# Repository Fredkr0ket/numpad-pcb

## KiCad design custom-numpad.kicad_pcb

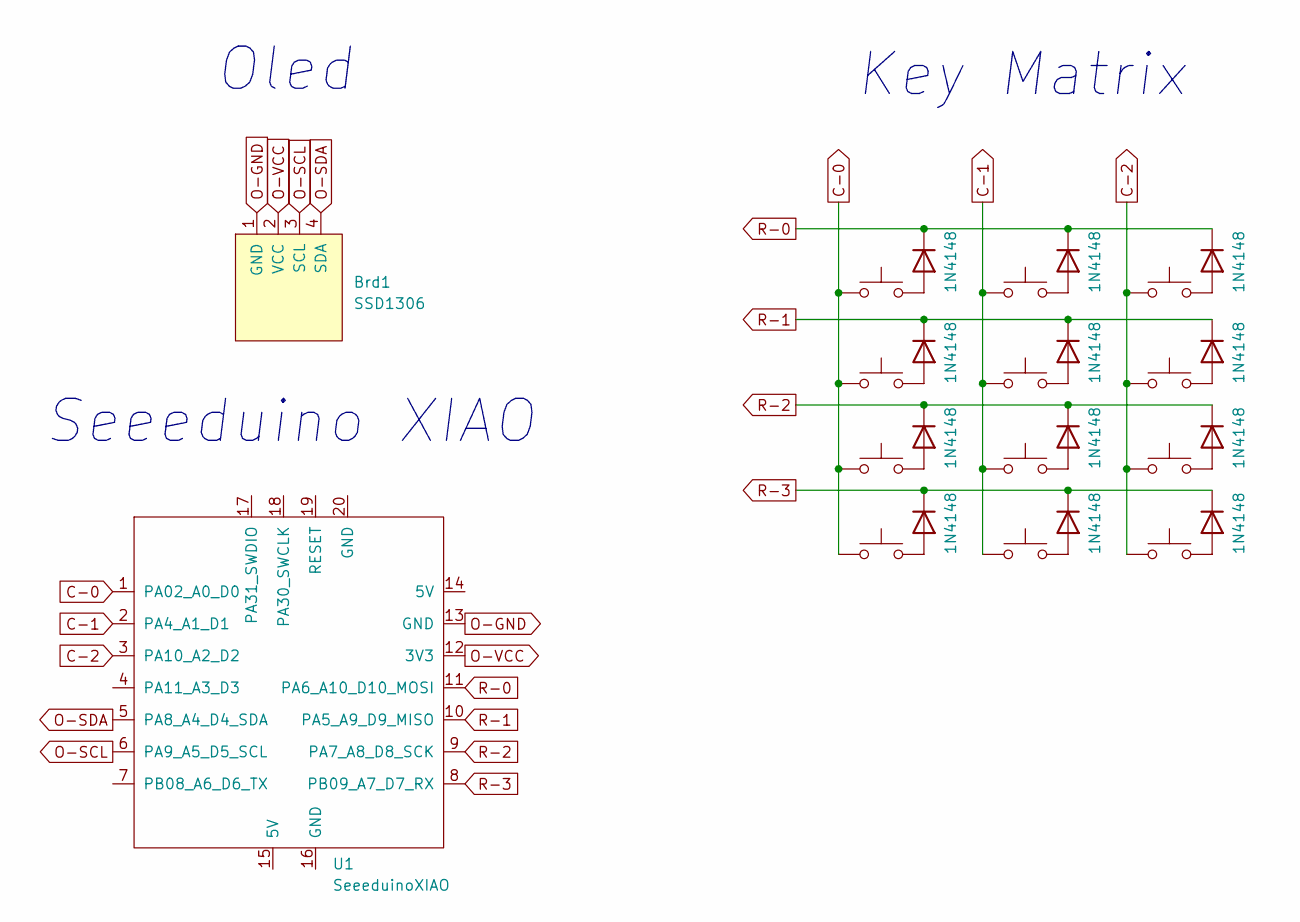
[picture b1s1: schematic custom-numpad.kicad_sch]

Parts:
Brd1: SSD1306; OLED_v2
D1, D2, D3, D4, D5, D6, D7, D8, D9, D10, D11, D12: 1N4148; D_DO-35_SOD27_P7.62mm_Horizontal
SW1, SW2, SW3, SW4, SW5, SW6, SW7, SW8, SW9, SW10, SW11, SW12: SW_Push; SW_Cherry_MX_1.00u_PCB
U1: SeeeduinoXIAO; MODULE_102010388

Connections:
C-0: SW1.1, SW10.1, SW11.1, SW12.1, U1.1 (PA02_A0_D0)
C-1: SW2.1, SW7.1, SW8.1, SW9.1, U1.2 (PA4_A1_D1)
C-2: SW3.1, SW4.1, SW5.1, SW6.1, U1.3 (PA10_A2_D2)
C-3: U1.4 (PA11_A3_D3)
unnamed: D1.2 (A), SW1.2
unnamed: D2.2 (A), SW2.2
unnamed: D3.2 (A), SW3.2
unnamed: D4.2 (A), SW12.2
unnamed: D5.2 (A), SW10.2
unnamed: D6.2 (A), SW9.2
unnamed: D7.2 (A), SW4.2
unnamed: D8.2 (A), SW7.2
unnamed: D9.2 (A), SW11.2
unnamed: D10.2 (A), SW8.2
unnamed: D11.2 (A), SW5.2
unnamed: D12.2 (A), SW6.2
O-GND: Brd1.1 (GND), U1.13 (GND)
O-SCL: Brd1.3 (SCL), U1.6 (PA9_A5_D5_SCL)
O-SDA: Brd1.4 (SDA), U1.5 (PA8_A4_D4_SDA)
O-VCC: Brd1.2 (VCC), U1.12 (3V3)
R-0: D1.1 (K), D2.1 (K), D3.1 (K), U1.11 (PA6_A10_D10_MOSI)
R-1: D5.1 (K), D6.1 (K), D7.1 (K), U1.10 (PA5_A9_D9_MISO)
R-2: D9.1 (K), D10.1 (K), D11.1 (K), U1.9 (PA7_A8_D8_SCK)
R-3: D4.1 (K), D8.1 (K), D12.1 (K), U1.8 (PB09_A7_D7_RX)

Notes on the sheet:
Key Matrix
Seeeduino XIAO
Oled

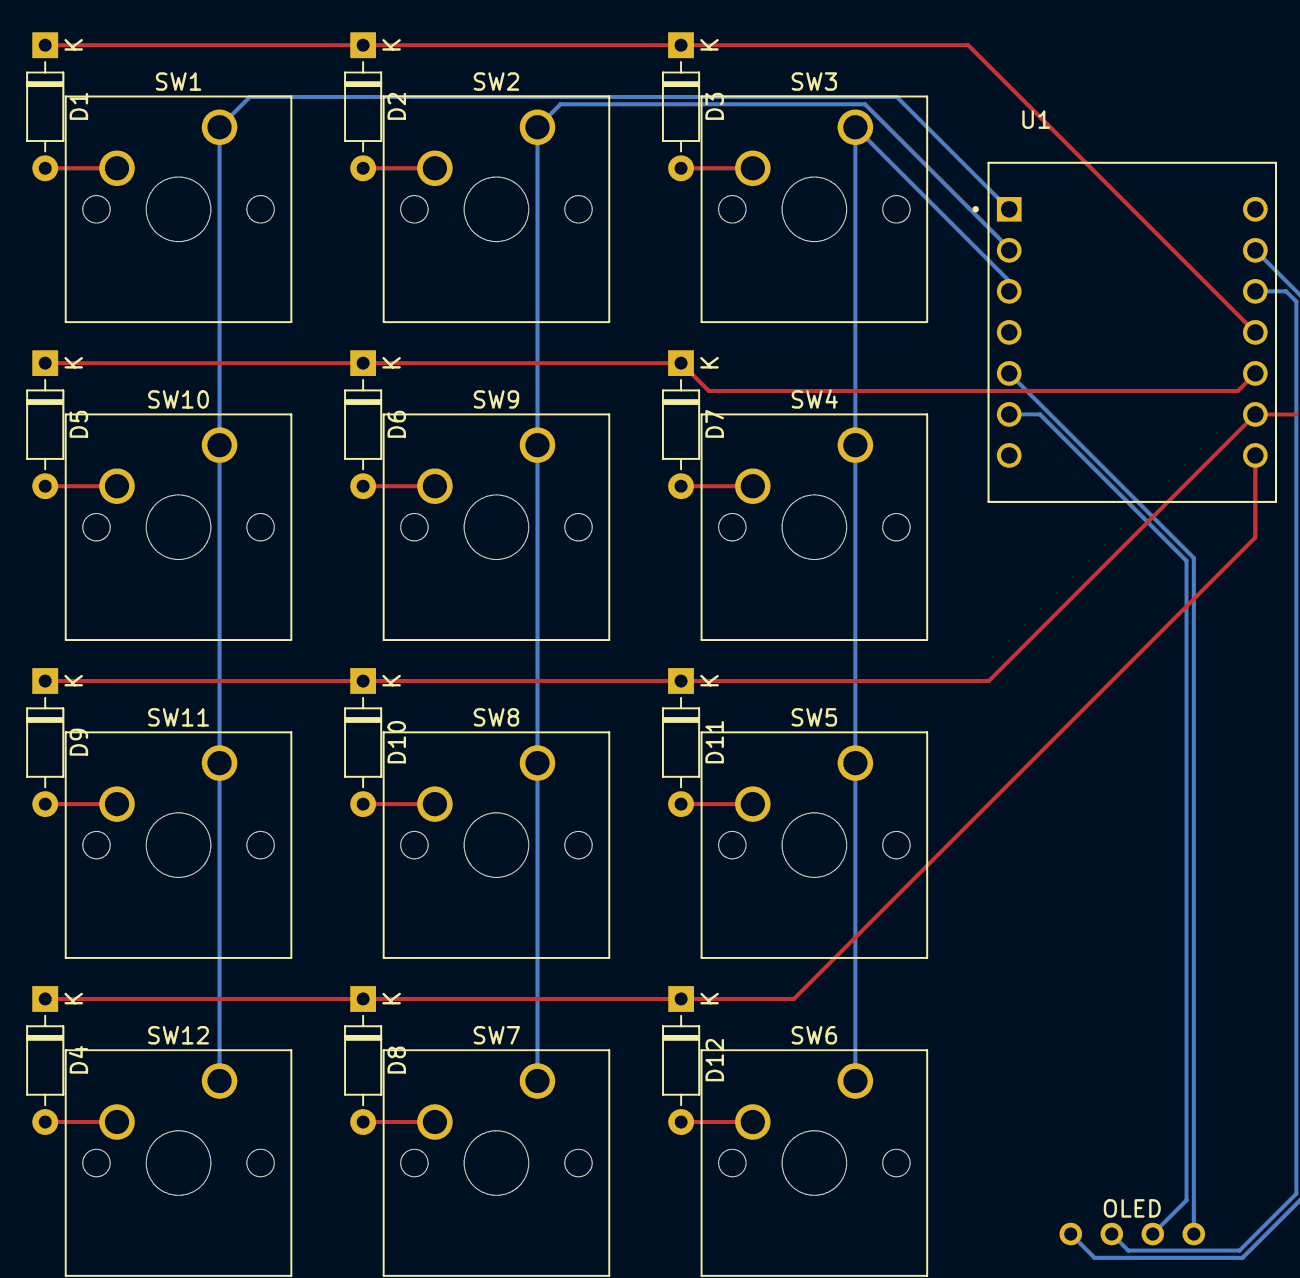
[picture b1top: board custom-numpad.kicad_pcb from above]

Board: 2 copper layers, 26 parts (0 on the bottom side), 23 nets.

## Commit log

2023-04-21 added numpad footprint
2023-04-21 made a start with the schematic
2023-04-29 added pad connections and local footprints and schematics
2023-05-08 wired up pcb inserted xiao blue print
